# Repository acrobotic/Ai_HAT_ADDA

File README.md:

## Ai\_HAT\_ADDA

PCB design files (EAGLE) of a Raspberry Pi A+/B+/2/3 HAT with four 16-Bit Analog
Inputs (ADS1115) and two 12-Bit Analog Outputs (MCP4725).

## Description

Visit our online shop at:

   * https://acrobotic.com/

Designed by ACROBOTIC Industries.  Please consider buying products from us to 
help fund future Open-Source projects like this! We’ll always put our best 
effort in every project, and release all our design files and code for you to 
use. 

## License

Released under the Creative Commons Attribution, Share-Alike license. Please 
check LICENSE.txt for more information. All text above must be included in any 
redistribution.

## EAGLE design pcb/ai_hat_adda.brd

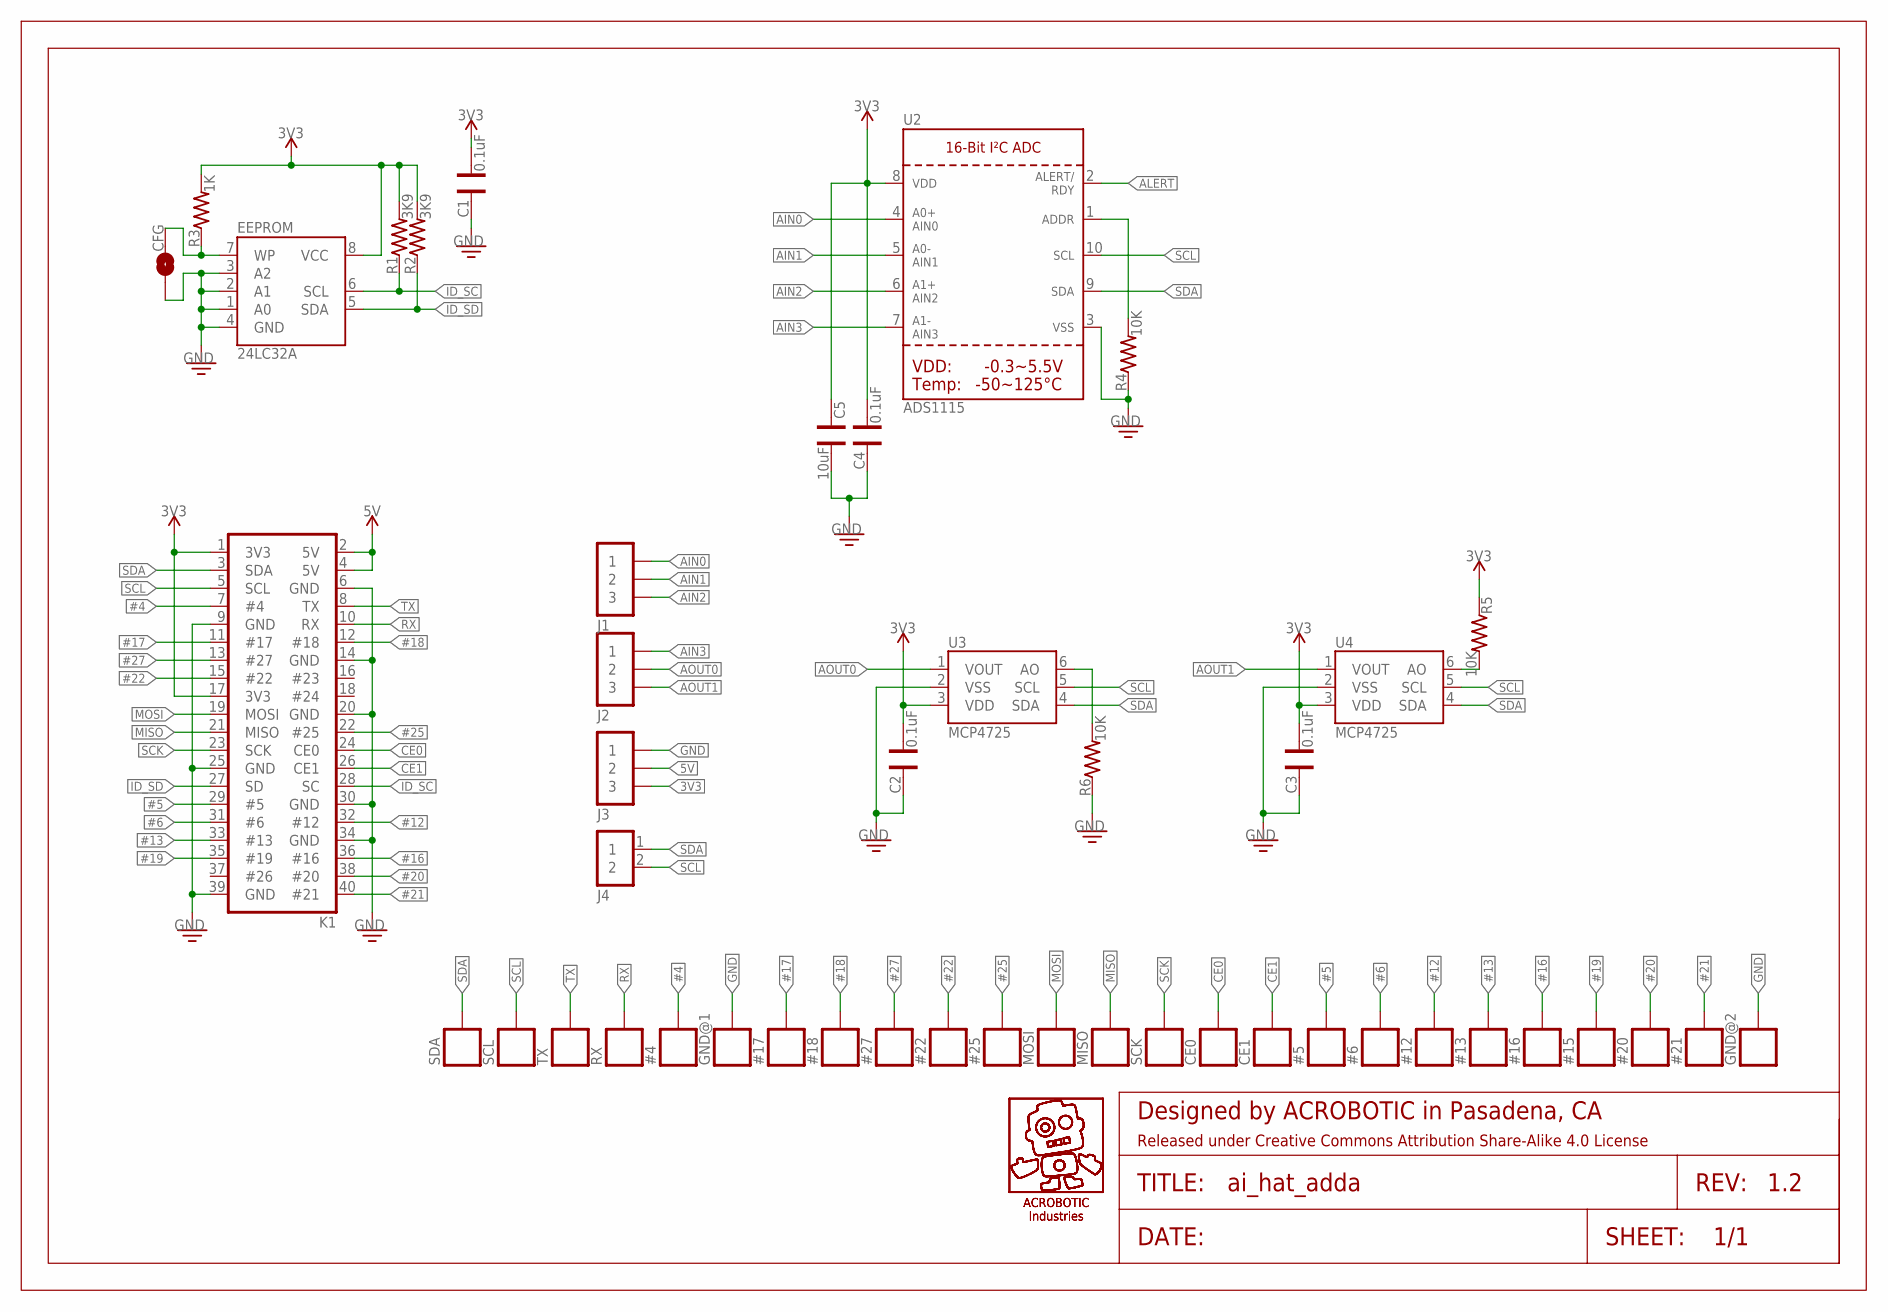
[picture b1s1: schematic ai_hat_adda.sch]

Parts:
#4, #5, #6, #12, #13, #15, #16, #17, #18, #20, #21, #22, #25, #27: 1X01-SM
C1: 0.1uF; CAP-0603
C2, C3, C4: 0.1uF; CAP-0402
C5: 10uF; CAP-0402
CE0, CE1: 1X01-SM
CFG: 1X02-SJ-NO
EEPROM: 24LC32A; SO08-EIAJ
FRAME1: FRAME-LETTER; CREATIVE-COMMONS
GND@1, GND@2: 1X01-SM
J1, J2, J3: 1X03ST; 1X03-ST
J4: 1X02ST; 1X02-ST
K1: 2X20-RPI-ALT
MISO: 1X01-SM
MOSI: 1X01-SM
R1, R2: 3K9; RES-0603; TOLERANCE 5%
R3: 1K; RES-0603; TOLERANCE 5%
R4, R5, R6: 10K; RES-0402
RX: 1X01-SM
SCK: 1X01-SM
SCL: 1X01-SM
SDA: 1X01-SM
TX: 1X01-SM
U2: ADS1115; MSOP10
U3, U4: MCP4725; SOT23-6
U$9, U$10: AI-LOGOXS; AI-LOGO-XS

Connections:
3V3: C1.1, C2.1, C3.1, C4.1, C5.2, EEPROM.8 (VCC), J3.3, K1.1 (3V3), K1.17 (3V3), R1.2, R2.2, R3.2, R5.1, U2.8 (VDD), U3.3 (VDD), U4.3 (VDD)
5V: J3.2, K1.2 (5V), K1.4 (5V)
#4: #4.1, K1.7 (#4)
#5: #5.1, K1.29 (#5)
#6: #6.1, K1.31 (#6)
#12: #12.1, K1.32 (#12)
#13: #13.1, K1.33 (#13)
#16: #16.1, K1.36 (#16)
#17: #17.1, K1.11 (#17)
#18: #18.1, K1.12 (#18)
#19: #15.1, K1.35 (#19)
#20: #20.1, K1.38 (#20)
#21: #21.1, K1.40 (#21)
#22: #22.1, K1.15 (#22)
#25: #25.1, K1.22 (#25)
#27: #27.1, K1.13 (#27)
AIN0: J1.1, U2.4 (AIN0)
AIN1: J1.2, U2.5 (AIN1)
AIN2: J1.3, U2.6 (AIN2)
AIN3: J2.1, U2.7 (AIN3)
ALERT: U2.2 (ALERT/RDY)
AOUT0: J2.2, U3.1 (VOUT)
AOUT1: J2.3, U4.1 (VOUT)
CE0: CE0.1, K1.24 (CE0)
CE1: CE1.1, K1.26 (CE1)
GND: C1.2, C2.2, C3.2, C4.2, C5.1, CFG.1, EEPROM.1 (A0), EEPROM.2 (A1), EEPROM.3 (A2), EEPROM.4 (GND), GND@1.1, GND@2.1, J3.1, K1.6 (GND), K1.9 (GND), K1.14 (GND), K1.20 (GND), K1.25 (GND), K1.30 (GND), K1.34 (GND), K1.39 (GND), R4.1, R6.1, U2.3 (VSS), U3.2 (VSS), U4.2 (VSS)
ID_SC: EEPROM.6 (SCL), K1.28 (SC), R1.1
ID_SD: EEPROM.5 (SDA), K1.27 (SD), R2.1
MISO: K1.21 (MISO), MISO.1
MOSI: K1.19 (MOSI), MOSI.1
unnamed: R4.2, U2.1 (ADDR)
unnamed: R6.2, U3.6 (AO)
unnamed: CFG.2, EEPROM.7 (WP), R3.1
unnamed: R5.2, U4.6 (AO)
RX: K1.10 (RX), RX.1
SCK: K1.23 (SCK), SCK.1
SCL: J4.2, K1.5 (SCL), SCL.1, U2.10 (SCL), U3.5 (SCL), U4.5 (SCL)
SDA: J4.1, K1.3 (SDA), SDA.1, U2.9 (SDA), U3.4 (SDA), U4.4 (SDA)
TX: K1.8 (TX), TX.1

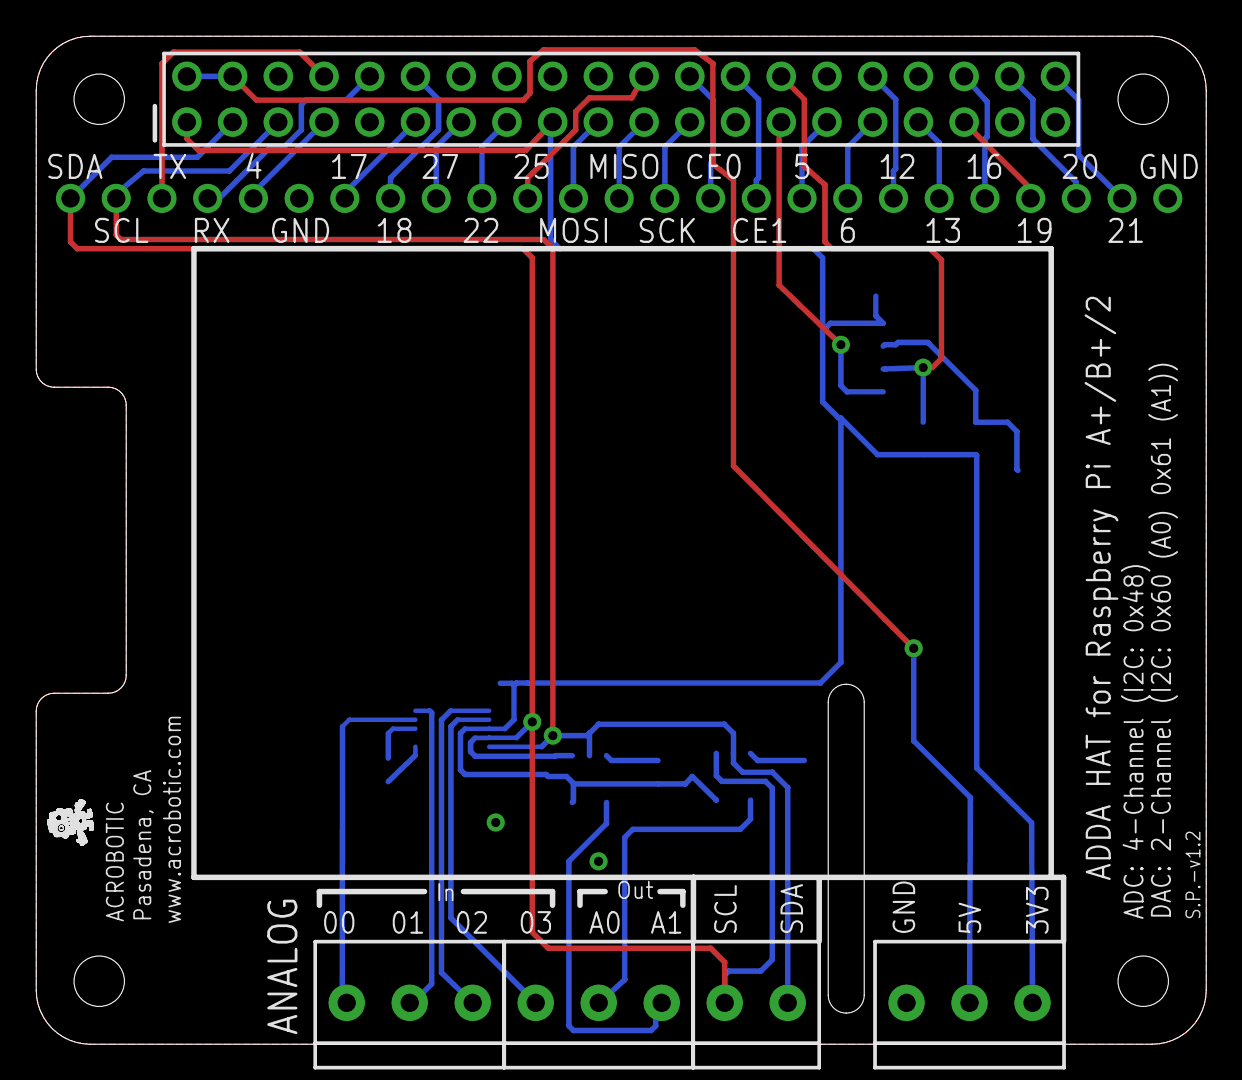
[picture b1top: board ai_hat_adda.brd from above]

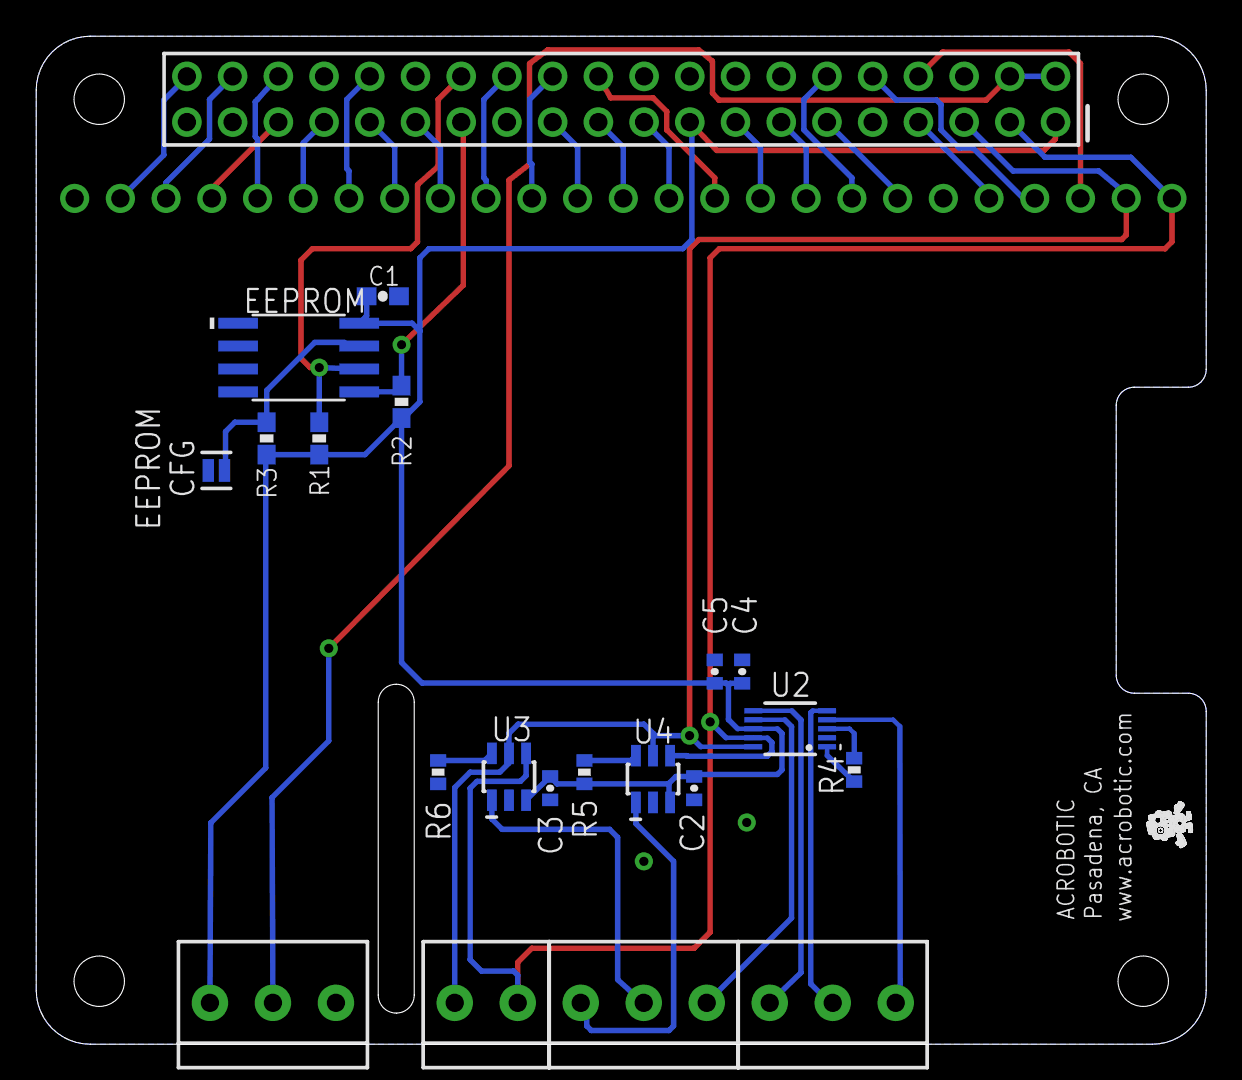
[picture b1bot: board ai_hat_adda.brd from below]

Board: 2 copper layers, 65.0 x 56.0 mm, 49 parts (17 on the bottom side), 38 nets.

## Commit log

2014-12-26 Small silkscreen change.
2014-12-28 updating supply to LEDs
2014-12-29 renaming
2015-04-24 latest update
2015-04-24 fixed accidental merger with Proto HAT. adding gerbers.
2015-04-25 minor silkscreen updates. added 3V3 output.
2015-04-25 updating
2015-06-29 fixed tracing problem.

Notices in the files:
parts and their libraries:
Ai_Miscellany: Attribution Share-Alike 4.0 License
Ai_Miscellany: https://creativecommons.org/licenses/by-sa/4.0
Ai_Miscellany: Released under Creative Commons Attribution Share-Alike 4.0 License
